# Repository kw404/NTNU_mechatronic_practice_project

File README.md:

# NTNU_mechatronic_practice_project

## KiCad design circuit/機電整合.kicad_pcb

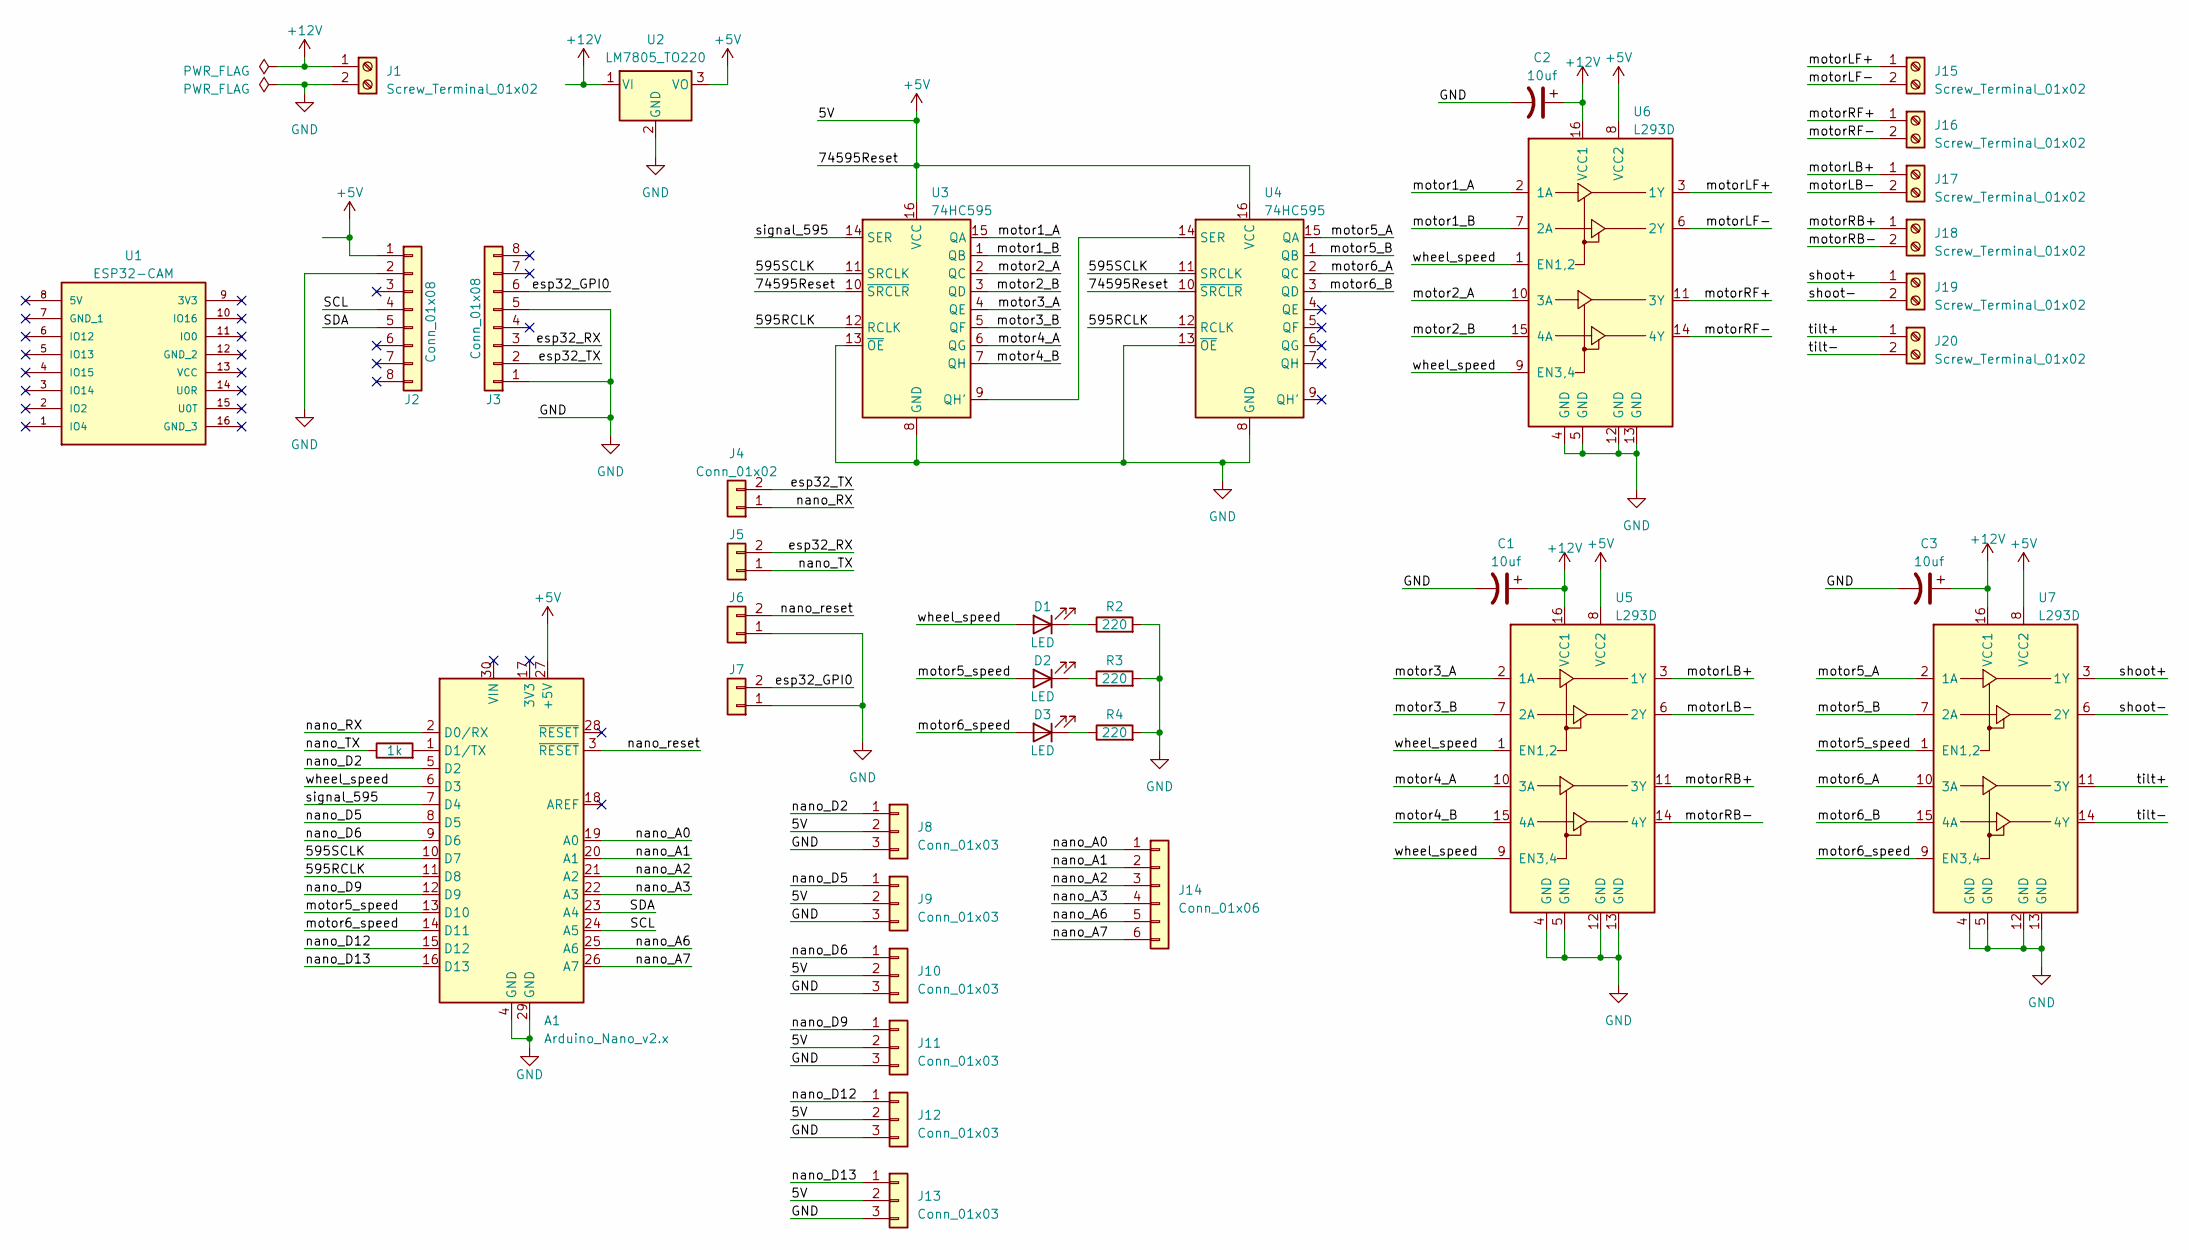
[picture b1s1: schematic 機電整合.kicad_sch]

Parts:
A1: Arduino_Nano_v2.x; Arduino_Nano
C1, C2, C3: 10uf; CP_Radial_D5.0mm_P2.50mm
D1, D2, D3: LED; LED_D3.0mm_FlatTop
J1, J15, J16, J17, J18, J19, J20: Screw_Terminal_01x02; HANDSON_KF301-2P
J2, J3: Conn_01x08; PinHeader_1x08_P2.54mm_Vertical
J4, J5, J6, J7: Conn_01x02; PinHeader_1x02_P2.54mm_Vertical
J8, J9, J10, J11, J12, J13: Conn_01x03; PinHeader_1x03_P2.54mm_Vertical
J14: Conn_01x06; PinHeader_1x06_P2.54mm_Vertical
R1: 1k; R_Axial_DIN0207_L6.3mm_D2.5mm_P10.16mm_Horizontal
R2, R3, R4: 220; R_Axial_DIN0207_L6.3mm_D2.5mm_P10.16mm_Horizontal
U1: ESP32-CAM; MANUFACTURER_PART_NUMBER ESP32-CAM
U2: LM7805_TO220; TO-220-3_Vertical
U3, U4: 74HC595; DIP-16_W7.62mm_Socket
U5, U6, U7: L293D; DIP-16_W7.62mm_Socket

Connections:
+5V: A1.27 (+5V), J2.1, J8.2, J9.2, J10.2, J11.2, J12.2, J13.2, U2.3 (VO), U3.10 (~SRCLR), U3.16 (VCC), U4.10 (~SRCLR), U4.16 (VCC), U5.8 (VCC2), U6.8 (VCC2), U7.8 (VCC2)
+12V: C1.1, C2.1, C3.1, J1.1, U2.1 (VI), U5.16 (VCC1), U6.16 (VCC1), U7.16 (VCC1)
/595RCLK: A1.11 (D8), U3.12 (RCLK), U4.12 (RCLK)
/595SCLK: A1.10 (D7), U3.11 (SRCLK), U4.11 (SRCLK)
/SCL: A1.24 (A5), J2.4
/SDA: A1.23 (A4), J2.5
/esp32_GPI0: J3.6, J7.2
/esp32_RX: J3.3, J5.2
/esp32_TX: J3.2, J4.2
/motor1_A: U3.15 (QA), U6.2 (1A)
/motor1_B: U3.1 (QB), U6.7 (2A)
/motor2_A: U3.2 (QC), U6.10 (3A)
/motor2_B: U3.3 (QD), U6.15 (4A)
/motor3_A: U3.4 (QE), U5.2 (1A)
/motor3_B: U3.5 (QF), U5.7 (2A)
/motor4_A: U3.6 (QG), U5.10 (3A)
/motor4_B: U3.7 (QH), U5.15 (4A)
/motor5_A: U4.15 (QA), U7.2 (1A)
/motor5_B: U4.1 (QB), U7.7 (2A)
/motor5_speed: A1.13 (D10), D2.2 (A), U7.1 (EN1,2)
/motor6_A: U4.2 (QC), U7.10 (3A)
/motor6_B: U4.3 (QD), U7.15 (4A)
/motor6_speed: A1.14 (D11), D3.2 (A), U7.9 (EN3,4)
/motorLB+: J17.1, U5.3 (1Y)
/motorLB-: J17.2, U5.6 (2Y)
/motorLF+: J15.1, U6.3 (1Y)
/motorLF-: J15.2, U6.6 (2Y)
/motorRB+: J18.1, U5.11 (3Y)
/motorRB-: J18.2, U5.14 (4Y)
/motorRF+: J16.1, U6.11 (3Y)
/motorRF-: J16.2, U6.14 (4Y)
/nano_A0: A1.19 (A0), J14.1
/nano_A1: A1.20 (A1), J14.2
/nano_A2: A1.21 (A2), J14.3
/nano_A3: A1.22 (A3), J14.4
/nano_A6: A1.25 (A6), J14.5
/nano_A7: A1.26 (A7), J14.6
/nano_D2: A1.5 (D2), J8.1
/nano_D5: A1.8 (D5), J9.1
/nano_D6: A1.9 (D6), J10.1
/nano_D9: A1.12 (D9), J11.1
/nano_D12: A1.15 (D12), J12.1
/nano_D13: A1.16 (D13), J13.1
/nano_RX: A1.2 (D0/RX), J4.1
/nano_TX: J5.1, R1.1
/nano_reset: A1.3 (~RESET), J6.2
/shoot+: J19.1, U7.3 (1Y)
/shoot-: J19.2, U7.6 (2Y)
/signal_595: A1.7 (D4), U3.14 (SER)
/tilt+: J20.1, U7.11 (3Y)
/tilt-: J20.2, U7.14 (4Y)
/wheel_speed: A1.6 (D3), D1.2 (A), U5.1 (EN1,2), U5.9 (EN3,4), U6.1 (EN1,2), U6.9 (EN3,4)
GND: A1.4 (GND), A1.29 (GND), C1.2, C2.2, C3.2, J1.2, J2.2, J3.1, J3.5, J6.1, J7.1, J8.3, J9.3, J10.3, J11.3, J12.3, J13.3, R2.2, R3.2, R4.2, U2.2 (GND), U3.8 (GND), U3.13 (~OE), U4.8 (GND), U4.13 (~OE), U5.4 (GND), U5.5 (GND), U5.12 (GND), U5.13 (GND), U6.4 (GND), U6.5 (GND), U6.12 (GND), U6.13 (GND), U7.4 (GND), U7.5 (GND), U7.12 (GND), U7.13 (GND)
unnamed: A1.1 (D1/TX), R1.2
unnamed: D1.1 (K), R2.1
unnamed: D2.1 (K), R3.1
unnamed: D3.1 (K), R4.1
unnamed: U3.9 (QH'), U4.14 (SER)

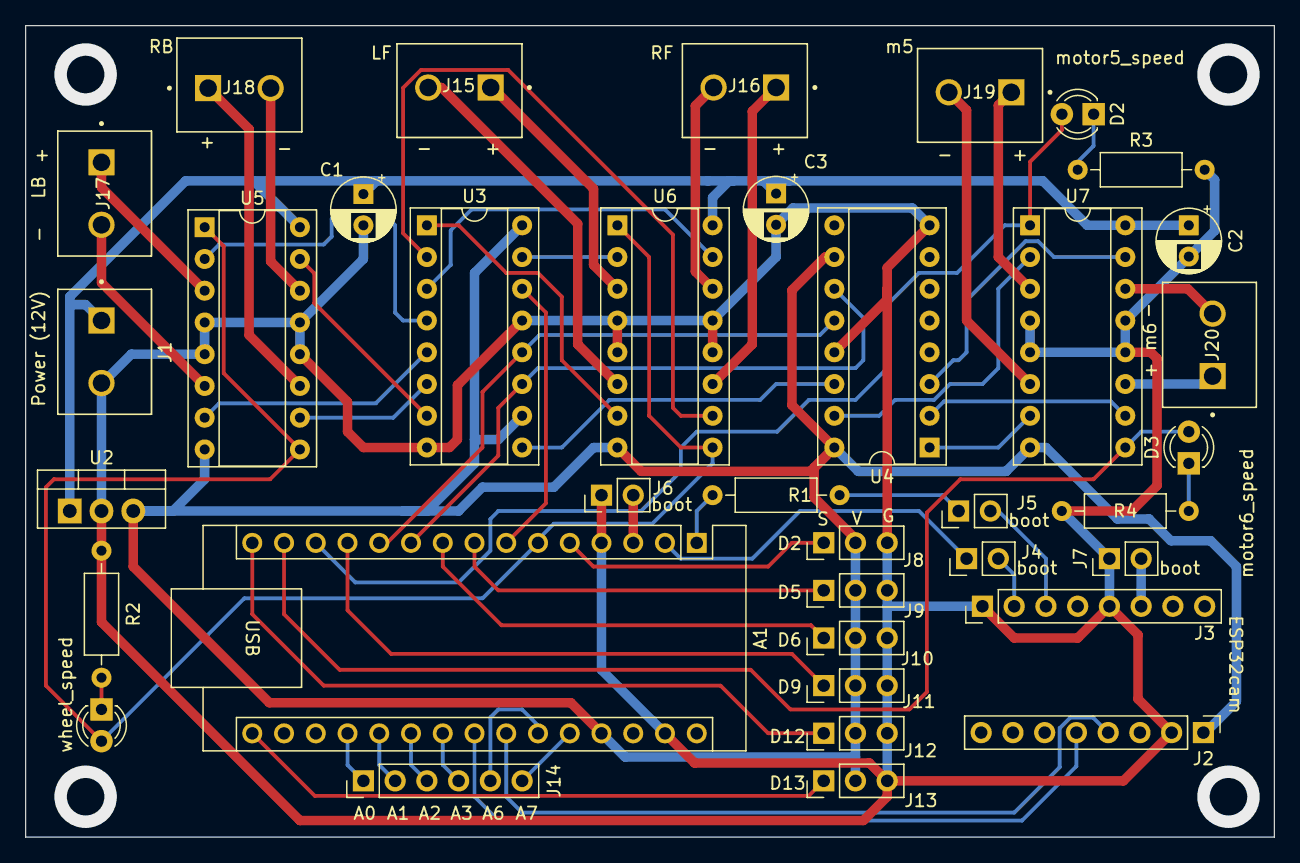
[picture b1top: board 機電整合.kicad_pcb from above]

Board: 2 copper layers, 99.9 x 64.9 mm, 37 parts (0 on the bottom side), 58 nets.

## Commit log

2023-04-19 html update
2023-05-13 add circuit part
2023-05-13 update circuit diagram
2023-05-13 program add
2023-05-13 nano pinout
2023-05-14 pcb done
2023-05-15 file name change
2023-06-23 upddate
